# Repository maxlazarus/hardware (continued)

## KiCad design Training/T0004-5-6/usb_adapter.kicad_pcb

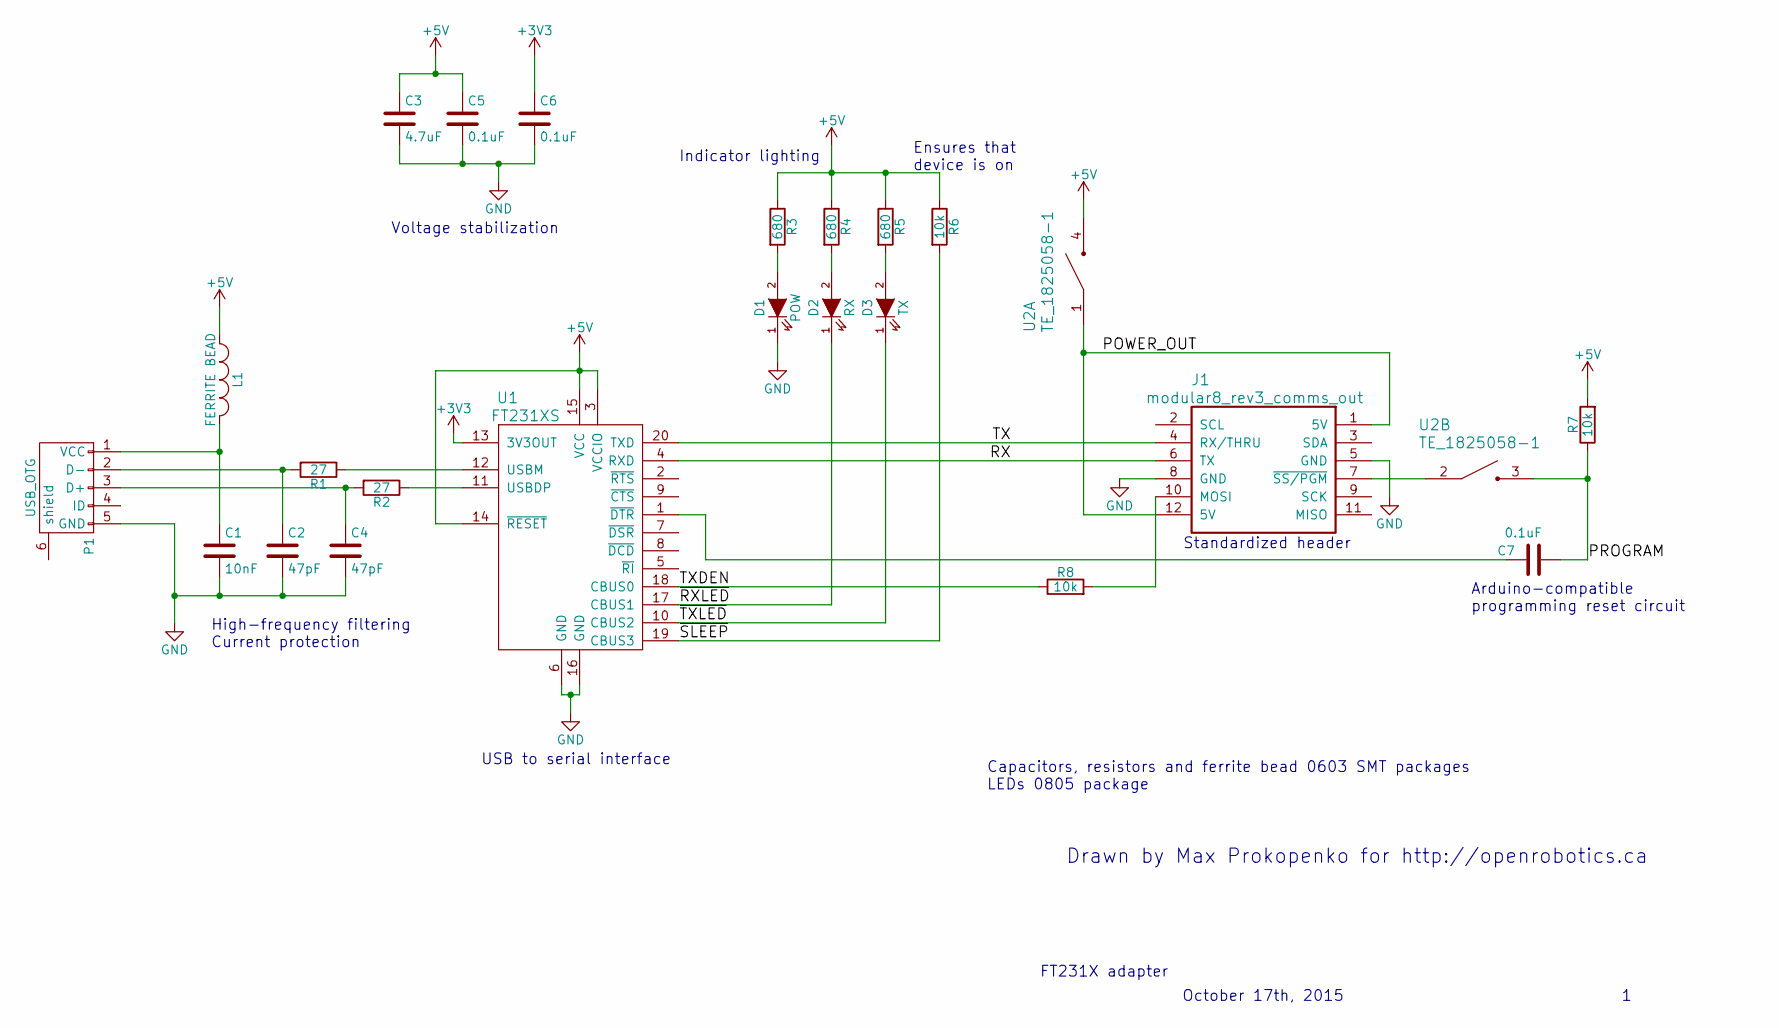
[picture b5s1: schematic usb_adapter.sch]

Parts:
C1: 10nF; C_0603
C2, C4: 47pF; C_0603
C3: 4.7uF; C_0603
C5, C6, C7: 0.1uF; C_0603
D1: POW; LED-0805
D2: RX; LED-0805
D3: TX; LED-0805
J1: modular8_rev3_comms_out; modular8_rev3_edge
L1: FERRITE BEAD; R_0603
P1: USB_OTG; USB_Mini-B
R1, R2: 27; R_0603
R3, R4, R5: 680; R_0603
R6, R7, R8: 10k; R_0603
U1: FT231XS; SSOP-20
U2: TE_1825058-1; DIPSWITCH_SMT_ALCO_2CCT

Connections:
+3V3: C6.1, U1.13 (3V3OUT)
+5V: C3.1, C5.1, L1.1, R3.1, R4.1, R5.1, R6.1, R7.2, U1.3 (VCCIO), U1.14 (~RESET), U1.15 (VCC), U2.4
/POWER_OUT: J1.1 (5V), J1.12 (5V), U2.1
/PROGRAM: C7.2, R7.1, U2.3
/RX: J1.6 (TX), U1.4 (RXD)
/TX: J1.4 (RX/THRU), U1.20 (TXD)
/TXDEN: R8.1, U1.18 (CBUS0)
/~RXLED: D2.1 (K), U1.17 (CBUS1)
/~SLEEP: R6.2, U1.19 (CBUS3)
/~TXLED: D3.1 (K), U1.10 (CBUS2)
GND: C1.2, C2.2, C3.2, C4.2, C5.2, C6.2, D1.1 (K), J1.5 (GND), J1.8 (GND), P1.5 (GND), U1.6 (GND), U1.16 (GND)
unnamed: C1.1, L1.2, P1.1 (VCC)
unnamed: C2.1, P1.2 (D-), R1.2
unnamed: C4.1, P1.3 (D+), R2.2
unnamed: C7.1, U1.1 (~DTR)
unnamed: D1.2 (A), R3.2
unnamed: D2.2 (A), R4.2
unnamed: D3.2 (A), R5.2
unnamed: J1.7 (~SS/PGM), U2.2
unnamed: J1.10 (MOSI), R8.2
unnamed: R1.1, U1.12 (USBM)
unnamed: R2.1, U1.11 (USBDP)

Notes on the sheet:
FT231X adapter
Drawn by Max Prokopenko for http://openrobotics.ca
October 17th, 2015
Capacitors, resistors and ferrite bead 0603 SMT packages LEDs 0805 package
High-frequency filtering Current protection
Voltage stabilization
USB to serial interface
Indicator lighting
Arduino-compatible programming reset circuit
Standardized header
Ensures that device is on

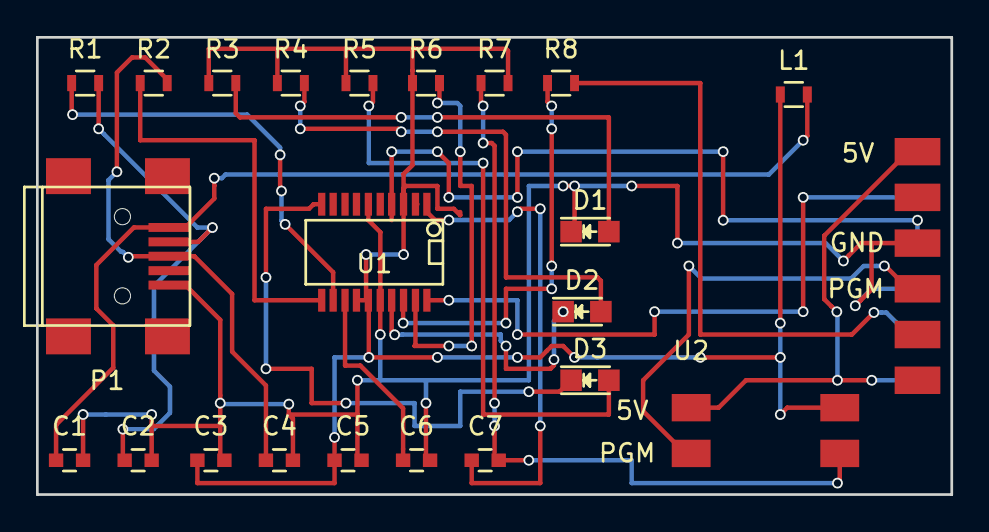
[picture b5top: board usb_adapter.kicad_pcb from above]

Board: 2 copper layers, 50.8 x 25.4 mm, 23 parts (0 on the bottom side), 22 nets.

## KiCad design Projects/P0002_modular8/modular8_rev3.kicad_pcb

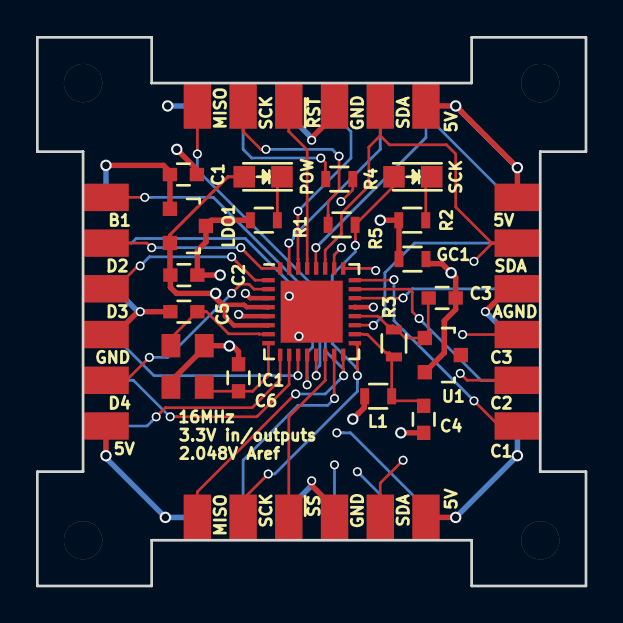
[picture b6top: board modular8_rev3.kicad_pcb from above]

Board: 4 copper layers, 30.5 x 30.5 mm, 23 parts (0 on the bottom side), 35 nets.

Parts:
16MHz: ABM8-16.000MHZ-10-1-U-T; CSMD-ABM8
C1, C2: 1uF; C_0603
C3, C4: 0.1uF; C_0603
C5, C6: 15pF; C_0603
GC1: 0; R_0603
IC1: ATMEGA328P-M; QFN-32-1EP_5x5mm_Pitch0.5mm
J1: modular8_rev3_comms_out; modular8_rev3_edge
J2: modular8_rev3_comms_in; modular8_rev3_edge
J3, J4: modular8_rev3_interface_master; modular8_rev3_edge
L1: 10uH; R_0603
LDO1: AP7313-33SAG-7; SOT-23
POW: POW; LED-0805
R1, R2: 680; R_0603
R3: 10k; R_0603
R4, R5: 39; R_0603
SCK: SCK; LED-0805
U1: LM4040D20IDBZR; SOT-23

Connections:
+5V: C1.1, J1.1, J1.12, J2.2, J2.11, J3.1, J3.12, J4.1, J4.12, LDO1.1
/2.048V: C3.1, IC1.20, R3.2, U1.1
/3V3: C2.1, IC1.4, IC1.6, L1.1, LDO1.2, POW.2
/ABUS0: IC1.23, J3.10
/ABUS1: IC1.24, J3.11
/ABUS2: IC1.25, J3.9
/ABUS3: IC1.26, J3.7
/ABUS4/SDA: IC1.27, J1.3, J2.9, J3.3
/ABUS5/SCL: IC1.28, J1.2, J2.12, J3.2
/ABUS6*: IC1.19, J3.4
/ABUS7*: IC1.22, J3.6
/DBUS0: IC1.12, J4.10
/DBUS1: IC1.13, J4.11
/DBUS2: IC1.32, J4.9
/DBUS3: IC1.1, J4.7
/DBUS4: IC1.2, J4.3
/DBUS5: IC1.9, J4.2
/DBUS6: IC1.10, J4.4
/DBUS7: IC1.11, J4.6
/MISO: IC1.16, J1.11, J2.1
/MOSI: IC1.15, J1.10, R5.1
/RX: IC1.30, J1.4, J2.8
/SCK: IC1.17, J1.9, R4.2, SCK.2
/TX: IC1.31, J1.6, J2.10
/~RST: IC1.29, J2.5
/~SS: IC1.14, J1.7
GND: 16MHz.2, 16MHz.4, C1.2, C2.2, C5.2, C6.2, GC1.1, IC1.3, IC1.5, J1.5, J1.8, J2.6, J2.7, J4.5, J4.8, LDO1.3, R1.2, R2.2
GNDA: C3.2, C4.2, GC1.2, IC1.21, J3.5, J3.8, U1.2
unnamed: C4.1, IC1.18, L1.2, R3.1
unnamed: 16MHz.1, C5.1, IC1.7
unnamed: 16MHz.3, C6.1, IC1.8
unnamed: POW.1, R1.1
unnamed: R2.1, SCK.1
unnamed: J2.3, R4.1
unnamed: J2.4, R5.2

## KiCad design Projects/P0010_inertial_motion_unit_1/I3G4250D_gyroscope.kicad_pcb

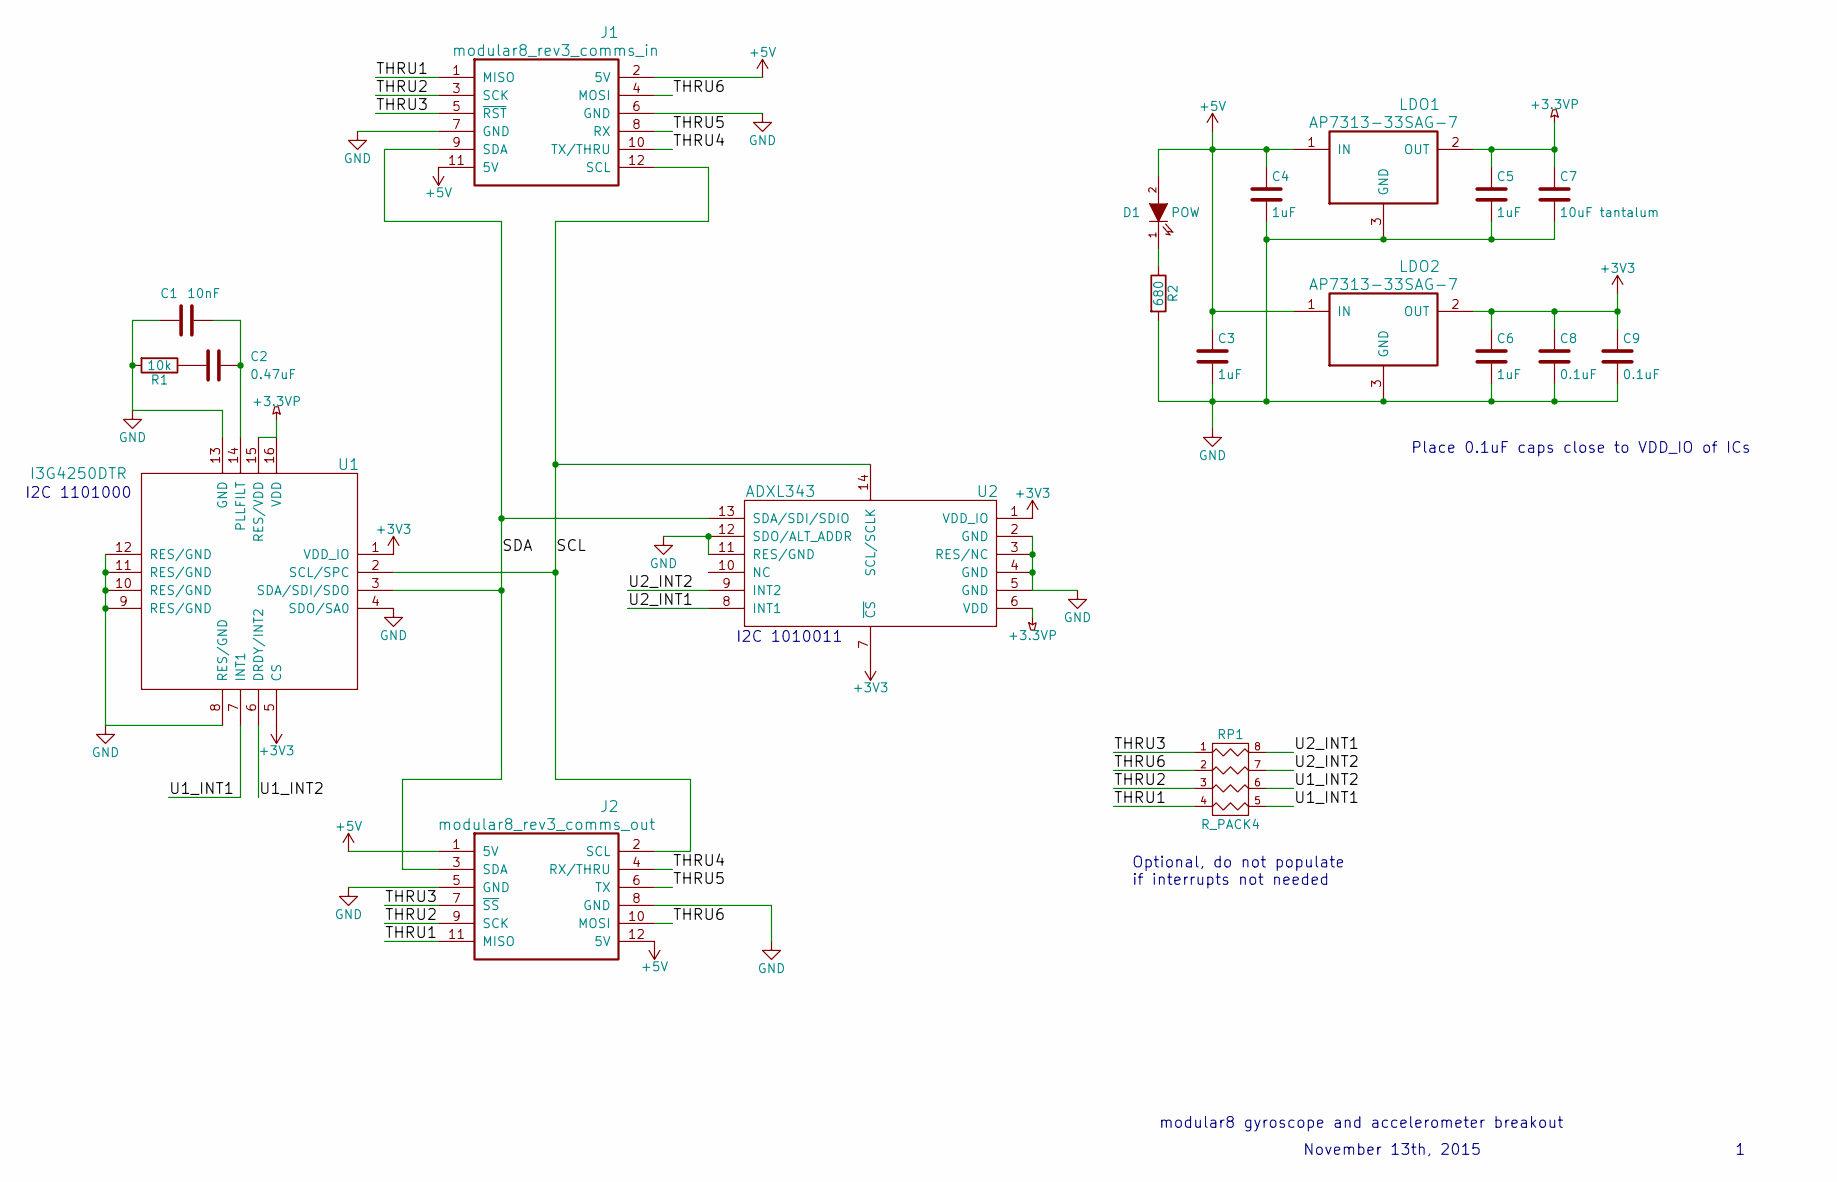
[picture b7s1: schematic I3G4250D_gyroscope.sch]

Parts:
C1: 10nF; C_0603
C2: 0.47uF; C_0603
C3, C4, C5, C6: 1uF; C_0603
C7: 10uF tantalum; C_0603
C8, C9: 0.1uF; C_0603
D1: POW; LED-0805
J1: modular8_rev3_comms_in; modular8_rev3_edge
J2: modular8_rev3_comms_out; modular8_rev3_edge
LDO1, LDO2: AP7313-33SAG-7; SOT-23
R1: 10k; R_0603
R2: 680; R_0603
RP1: R_PACK4; R_Array_Convex_4x0603
U1: I3G4250DTR; LGA-16
U2: ADXL343; LGACC-14-1

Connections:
+3.3VP: C5.1, C7.1, LDO1.2 (OUT), U1.15 (RES/VDD), U1.16 (VDD), U2.6 (VDD)
+3V3: C6.1, C8.1, C9.1, LDO2.2 (OUT), U1.1 (VDD_IO), U1.5 (CS), U2.1 (VDD_IO), U2.7 (~CS)
+5V: C3.1, C4.1, D1.2 (A), J1.2 (5V), J1.11 (5V), J2.1 (5V), J2.12 (5V), LDO1.1 (IN), LDO2.1 (IN)
/SCL: J1.12 (SCL), J2.2 (SCL), U1.2 (SCL/SPC), U2.14 (SCL/SCLK)
/SDA: J1.9 (SDA), J2.3 (SDA), U1.3 (SDA/SDI/SDO), U2.13 (SDA/SDI/SDIO)
/THRU1: J1.1 (MISO), J2.11 (MISO), RP1.4
/THRU2: J1.3 (SCK), J2.9 (SCK), RP1.3
/THRU3: J1.5 (~RST), J2.7 (~SS), RP1.1
/THRU4: J1.10 (TX/THRU), J2.4 (RX/THRU)
/THRU5: J1.8 (RX), J2.6 (TX)
/THRU6: J1.4 (MOSI), J2.10 (MOSI), RP1.2
/U1_INT1: RP1.5 (R4), U1.7 (INT1)
/U1_INT2: RP1.6 (R3), U1.6 (DRDY/INT2)
/U2_INT1: RP1.8 (R1), U2.8 (INT1)
/U2_INT2: RP1.7 (R2), U2.9 (INT2)
GND: C1.2, C3.2, C4.2, C5.2, C6.2, C7.2, C8.2, C9.2, J1.6 (GND), J1.7 (GND), J2.5 (GND), J2.8 (GND), LDO1.3 (GND), LDO2.3 (GND), R1.2, R2.2, U1.4 (SDO/SA0), U1.8 (RES/GND), U1.9 (RES/GND), U1.10 (RES/GND), U1.11 (RES/GND), U1.12 (RES/GND), U1.13 (GND), U2.2 (GND), U2.3 (RES/NC), U2.4 (GND), U2.5 (GND), U2.11 (RES/GND), U2.12 (SDO/ALT_ADDR)
unnamed: C1.1, C2.1, U1.14 (PLLFILT)
unnamed: C2.2, R1.1
unnamed: D1.1 (K), R2.1

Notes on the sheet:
I2C 1101000
I2C 1010011
Place 0.1uF caps close to VDD_IO of ICs
Optional, do not populate if interrupts not needed
modular8 gyroscope and accelerometer breakout
November 13th, 2015

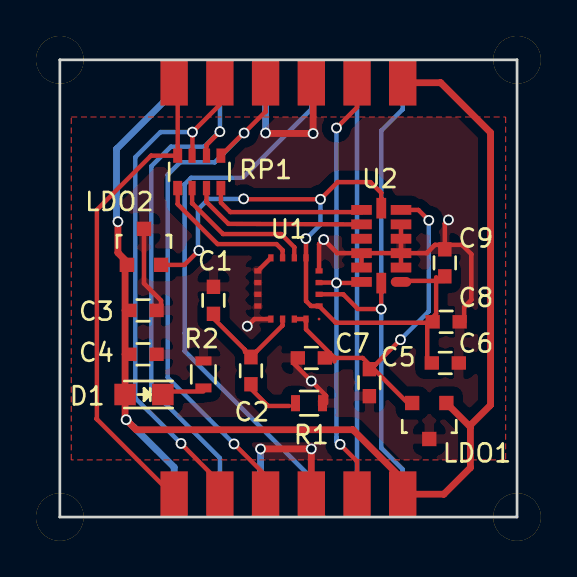
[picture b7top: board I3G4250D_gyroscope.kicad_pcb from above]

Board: 2 copper layers, 25.4 x 25.4 mm, 19 parts (0 on the bottom side), 19 nets.

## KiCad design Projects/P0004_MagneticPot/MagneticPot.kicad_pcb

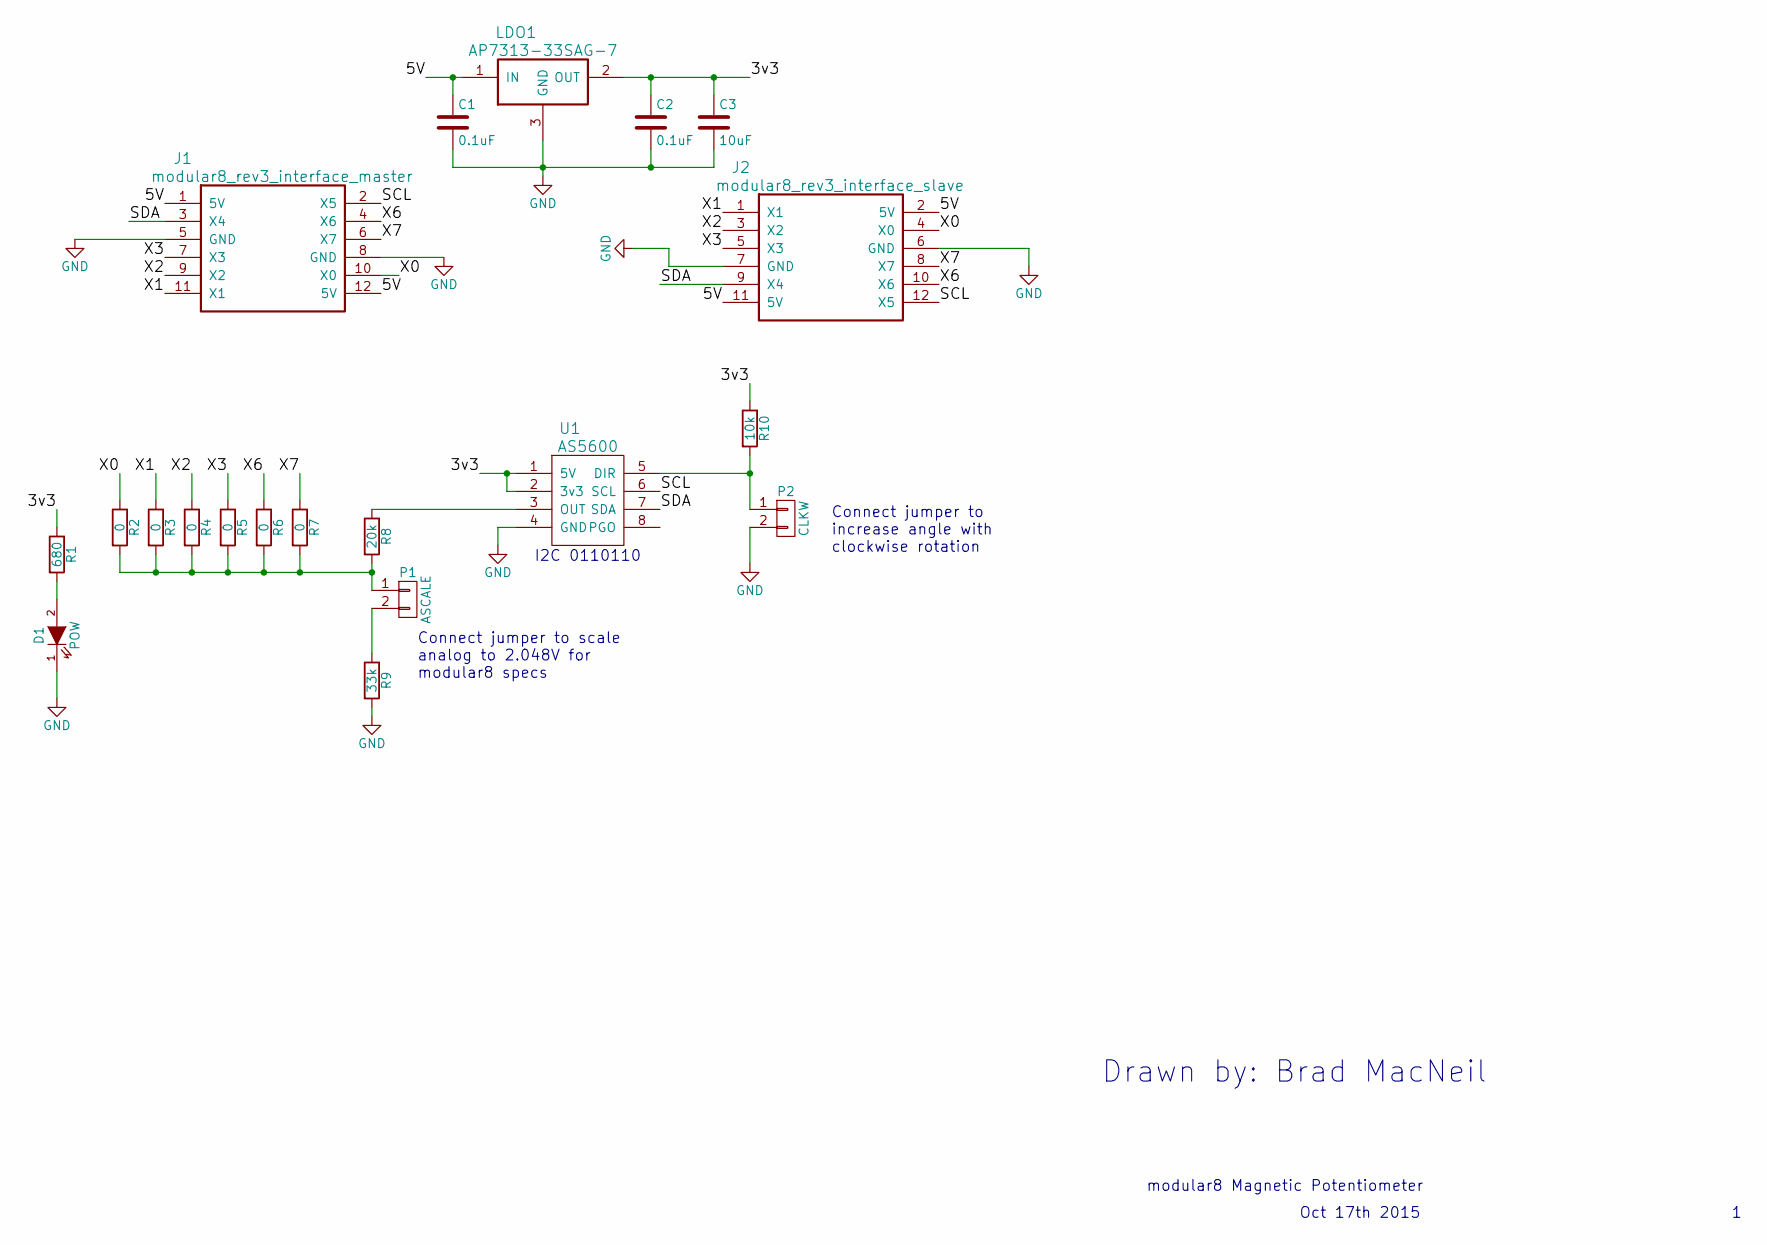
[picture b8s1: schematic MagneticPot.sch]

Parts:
C1, C2: 0.1uF; C_0603
C3: 10uF; C_0603
D1: POW; LED-0805
J1: modular8_rev3_interface_master; modular8_rev3_edge
J2: modular8_rev3_interface_slave; modular8_rev3_edge
LDO1: AP7313-33SAG-7; SOT-23
P1: ASCALE; Pin_Header_Straight_1x02
P2: CLKW; Pin_Header_Straight_1x02
R1: 680; R_0603
R2, R3, R4, R5, R6, R7: 0; R_0603
R8: 20k; R_0603
R9: 33k; R_0603
R10: 10k; R_0603
U1: AS5600; SOIC-8-N

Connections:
/3v3: C2.1, C3.1, LDO1.2 (OUT), R1.1, R10.1, U1.1 (5V), U1.2 (3v3)
/5V: C1.1, J1.1 (5V), J1.12 (5V), J2.2 (5V), J2.11 (5V), LDO1.1 (IN)
/SCL: J1.2 (X5), J2.12 (X5), U1.6 (SCL)
/SDA: J1.3 (X4), J2.9 (X4), U1.7 (SDA)
/X0: J1.10 (X0), J2.4 (X0), R2.1
/X1: J1.11 (X1), J2.1 (X1), R3.1
/X2: J1.9 (X2), J2.3 (X2), R4.1
/X3: J1.7 (X3), J2.5 (X3), R5.1
/X6: J1.4 (X6), J2.10 (X6), R6.1
/X7: J1.6 (X7), J2.8 (X7), R7.1
GND: C1.2, C2.2, C3.2, D1.1 (K), J1.5 (GND), J1.8 (GND), J2.6 (GND), J2.7 (GND), LDO1.3 (GND), P2.2, R9.2, U1.4 (GND)
unnamed: D1.2 (A), R1.2
unnamed: P1.1, R2.2, R3.2, R4.2, R5.2, R6.2, R7.2, R8.2
unnamed: P1.2, R9.1
unnamed: P2.1, R10.2, U1.5 (DIR)
unnamed: R8.1, U1.3 (OUT)

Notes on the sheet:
Drawn by: Brad MacNeil
modular8 Magnetic Potentiometer
Oct 17th 2015
I2C 0110110
Connect jumper to scale analog to 2.048V for modular8 specs
Connect jumper to increase angle with clockwise rotation

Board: 2 copper layers, 20 parts (0 on the bottom side), 16 nets, no tracks yet.

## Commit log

2015-09-24 starting hardware repo
2015-09-24 transferred hardware files in
2015-09-26 renamed dir
2015-09-26 directory naming...
2015-09-26 training directory added
2015-09-28 starting gyro research
2015-09-28 moved gyro into projects
2015-10-02 started IMU project
2015-10-03 finished training schematic, seperated folders
2015-10-03 updated header standards
2015-10-06 started rev3 of the 328p module
2015-10-13 started P0003 LED display, P0002 PCB layout
2015-10-18 Started P0004 up to PCB layout
2015-10-19 started routing modular8_rev3
2015-10-19 testing pushing from new location
2015-10-19 first pass at routing
2015-10-19 fixed 1 unconnected
2015-10-20 generated Gerber files
2015-10-20 Added extra silkscreen info, README
2015-10-20 corrected gerber package
2015-10-21 started AT90 programmer P0005
2015-10-23 added schematic for training sessions, reorganized
2015-10-23 added updated schematic image for T0003
2015-10-23 corrected folder names
2015-10-23 fixed training schematic
2015-10-31 upload for checking design
2015-10-31 redy for design to be checked
2015-10-31 ready for designs to be checked
2015-10-31 ready for design to be checked (check the file with 'ver4')
2015-10-31 ready for design to be checked
2015-11-04 working through training session...
2015-11-07 saved new library path
2015-11-07 added proper FT231 components
2015-11-07 footprint fixes
2015-11-07 added suggestions
2015-11-07 fixed footprint filter
2015-11-07 footprint updates and comments
2015-11-07 updated footprints and suggestions
2015-11-07 fixed footprints, added suggestions
2015-11-07 fixed footprints
2015-11-08 fixed switch footprint
2015-11-14 updated master schematic
2015-11-14 moved gyro/accel to Projects
2015-11-14 generated gerbers, ordered P0010
2015-11-14 updated gerbers
2015-11-14 updated files
2015-11-14 uploading initial design
2015-11-14 finished
2015-11-14 made my fixes - max
2015-11-14 forgot to save schematic - updated
2015-11-14 finished routing after fix
2015-11-14 original work
2015-11-14 initial schematics
2015-11-14 included working files
2015-11-19 first commit to personal brannch
2015-11-21 changed name of AVR ICSP programmer
2015-11-21 changed 10k to 1k for vref m8_rev3
2015-11-21 fixed my mistakes - Max
2015-11-21 overrode autosave
2015-11-26 added bus driver schematic
2015-11-28 first commit to personal branch
2015-11-30 added finished gerbers
2015-12-01 max fixing footprint mistakes
2015-12-01 added gerber files
2015-12-01 final pcb design submission
2015-12-01 max - added solder mask needed
2015-12-03 generated gerbers
2015-12-04 added gerbers for all
2015-12-23 updated by Max
2015-12-23 moved datasheets, added gerbers for Kevin
2016-01-04 added datasheet
2016-01-04 Actually started Blunderbot project folder
2016-01-24 Added some datasheets, started p0014_rev1 schematic
2016-01-25 First pass at P0014rev1 schematic
2016-01-27 Added a circuit sim
2016-01-31 Updated module rev3
2016-02-03 Started power distribution unit
2016-02-10 Moved out datasheets, made 1 footprint
2016-02-13 More work on PDU schematic
2016-02-21 Updated USB footprint and rails to 5V
2016-02-21 Layout pt 1
2016-02-22 layout nearly done
2016-02-22 layout first pass finished, need to update gerbers for seeed
2016-03-08 finishing routing on bus adapter
2016-03-19 updated project 8
2016-03-23 revised P0008, added gerbers
2016-05-21 did some updates I guess?
2016-07-19 Simplifying PDU
2016-07-21 Simplified power on switch
2016-08-03 Started layout for PDU module
2016-08-19 Started rev2
2016-11-05 Updated pdf for RS485 interface driver
2016-11-06 Almost done placement for P0016
2016-11-19 Created RS485 to TTL adapter
